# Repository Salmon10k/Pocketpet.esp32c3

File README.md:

# Pocketpet.esp32c3

> **Status (2026-11-14): active again, in small steps.** The project was paused on 2026-10-30 and picked back up
> for the games/menu revamp (11-12) and a repo review (11-14). A lot of the firmware on `main` (Online, Spotify,
> Lyrics visual, games, launcher) is still **not fully tested on the device**, and the custom PCB is designed but
> not finished or ordered (`PCB/` holds the KiCad project only). See `HANDOFF.md` for the details.
> Do not start big new features unless Salman asks.

Keychain-sized digital pet gadget built around an ESP32-C3 Super Mini with a 1.3" SH1106 OLED, MPU6050 motion sensor, touch input and three buttons.

## Current hardware wiring

**Important:** the OLED and MPU6050 share **one hardware I2C bus (`Wire`)** on GPIO 8 (SDA) and GPIO 9 (SCL), 400 kHz. They have different addresses (OLED `0x3C`, MPU6050 `0x68`), so they coexist on the same two wires. (Until 2026-11-09 the MPU6050 was on its own software I2C bus on GPIO 5/6; that is gone and GPIO 5/6 are free.)

| Part | Pin | ESP32-C3 GPIO | Notes |
|------|-----|---------------|-------|
| OLED SH1106 + MPU6050 | SDA | **8** | Shared hardware I2C, 400 kHz |
| OLED SH1106 + MPU6050 | SCL | **9** | Shared hardware I2C, 400 kHz |
| Button A | one leg to GND | **2** | Up / previous / tickle |
| Button B | one leg to GND | **1** | Select / back |
| Button C | one leg to GND | **0** | Down / next / boop |
| Touch pad | OUT | **4** | TTP223-style, HIGH when touched (the pin next to 3V3) |

Wire the MPU6050 SDA/SCL to the same GPIO 8 / 9 pins as the OLED.

### I2C addresses
- OLED: `0x3C`
- MPU6050: `0x68`

### GPIO notes
- GPIO 8 and GPIO 9 are ESP32-C3 strapping pins (they are also the C3's default I2C pins). The OLED has been tested on them. If the board ever becomes unreliable during boot, investigate these pins first.
- GPIO3 is the only free ADC1 pin left. Keep it for the battery voltage divider.
- GPIO 0-5 can wake the C3 from deep sleep, so the touch pad (GPIO4) and buttons (0, 1, 2) all work for wake-up later.

## Current firmware

### Home and menu
The **pet is the home screen**: it is what you see when the keychain turns on and where it returns to when you leave it alone (the launcher goes back to the pet after 20 s without input; holding B in the launcher also goes home). **Press B on the pet** to open the launcher, which has two styles you pick in **Settings > Menu style**:
- **Carousel** (default): big icons slide in from the right; **A** = previous, **C** = next, **B** = open.
- **Tilt ring**: the apps sit on a ring; **tilt the keychain toward an app** to highlight it, **B** opens it (A/C also step through them).

In the launcher: Fluid, Stats, Motion test, Tools, Games, Online, Spotify, Visualizer (Lyrics visual), Living OLED, Settings. While it starts, the MPU6050 calibrates itself in the background (gyro offsets, and which way is "down" from gravity), so tilt works however the sensor sits on the board and however you hold the keychain; in Pet mode it re-levels itself when you hold it still in a new pose. Every sub-menu (Tools, Games, Settings and the Online list) uses the same carousel / tilt-ring look as the home screen: **A/C** move, short **B** opens, **hold B** goes up one level, and each one ends with a **Back** item. Settings shows the current value in a pill under the name (brightness, screen auto-off, flip screen, menu style, lyrics sync, reset pet); Games shows your best score. Tools contains Temperature, Magic 8-ball and Dice (shake the keychain to roll / ask).

### Games
Built for the three buttons and the MPU6050. Best scores are saved.

| Game | Controls |
|------|----------|
| **Star Blaster** (side-scrolling shooter: drones, gunships, splitting rocks, power-ups) | tilt flies the ship, **A** shoots (hold = rapid fire), **C** = smart bomb |
| **Sniper** (night city, scope with sway; enemies pop up in windows, survive 3 misses) | tilt swings the scope, **A** fires (bolt action), hold **C** to steady your breath and zoom 2x |
| **Road Rush** (pseudo-3D racer, beat the clock, checkpoints add time) | tilt steers (bends push you outwards), **A** nitro, **C** brake |
| **Pinball** (the table lies on its side, flippers on the right edge) | **A** upper flipper, **C** lower flipper, shake the keychain to nudge the ball (nudge too much = TILT) |
| **Tilt Maze** | tilt, **A** re-zero, **C** new maze |
| **Snake** | tilt to steer (or **A** left / **C** right) |

Online has 12 screens that need the internet (see below). Copy `src/secrets.example.h` to `src/secrets.h` and set `WIFI_SSID` / `WIFI_PASSWORD` locally first. The touch pad only works in Pet mode.

### Online mode
Wi-Fi stays **off** everywhere except Online mode. Entering Online connects **once** (up to 3 automatic attempts, then each request is retried up to 3 times for random network hiccups), fetches everything for every screen in one go, and stays connected while you browse. Leaving Online switches the radio off. The list header shows the state: `wifi 2/3`, `sync 4/9`, `online`, `offline`. Every screen shows how old its data is (top right). If a refresh fails you keep the last good data.

**Several Wi-Fi networks:** list them in `secrets.h` with `WIFI_NETWORKS` (see `src/secrets.example.h`), for example home, uni and your phone hotspot. On entering Online it scans, tries the strongest known network first and falls back to the others by itself. Net status shows which one it picked. 2.4 GHz networks only.

Controls: in the list, A/C move and B opens (**Sync now** refetches everything, **Back** leaves). On a screen, **A = refresh this screen** (no reconnect), **C = next screen**, **B = back to the list**, touch = Home.

| Screen | Source (no API keys) | Refreshes |
|--------|----------------------|-----------|
| Clock | NTP (`pool.ntp.org`), keeps ticking offline | synced on connect, resync every 6 h |
| Weather | Open-Meteo | 30 min |
| Forecast | same request as Weather | 30 min |
| Air quality | Open-Meteo air quality (US AQI, PM2.5) | 30 min |
| Currency | open.er-api.com (USD to `CURRENCY_HOME`, EUR, GBP) | 6 h |
| World clocks | computed from NTP time, with DST rules for London, New York, Tokyo, Sydney | no request |
| Random fact | uselessfacts.jsph.pl | once per visit, A = new one |
| Advice | adviceslip.com | once per visit, A = new one |
| Moon phase | calculated from the date (approximate, within about a day) | no request |
| Net status | RSSI, IP, a `generate_204` check with ping time | every 20 s while open |
| ISS tracker | api.open-notify.org (plain HTTP) | every 60 s while open |
| GitHub | api.github.com stars, forks, issues, last push | 10 min |

Location for weather and air quality comes from an IP lookup (ip-api.com) unless you set `LOCATION_LAT` / `LOCATION_LON` in `secrets.h`. See `src/secrets.example.h` for all optional overrides.

**Pet reactions:** when cached data exists, Pet mode shows tiny corner icons: sweat drop (35 C or hotter), umbrella (rain chance 60% or more), cloud (AQI 150 or more), moon (after sunset). Each successful fetch also gives the pet a small happiness bump.

Requests are blocking with a 7 second timeout, so the screen can pause briefly while one runs. A progress frame is drawn first so it never looks frozen. Background refresh while you are in Online: weather and air quality every 30 min, currency 6 h, GitHub 10 min. Net status and ISS only refresh while you are looking at them.

**Connection problems:** many ESP32-C3 Super Mini boards fail to connect at full TX power, so the firmware lowers it to 8.5 dBm by default. If your router is far away and the signal is weak, put `#define WIFI_TX_POWER WIFI_POWER_11dBm` (or `WIFI_POWER_19_5dBm`) in `src/secrets.h`.

### Spotify mode
Shows what is playing on your Spotify (any device: phone, PC, speaker), with **synced lyrics** from LRCLIB, and controls it: **A** previous, **B** play/pause, **C** next. **Hold B** (0.7 s) = back to the menu. The screen stays on while you are in this mode. Needs Spotify **Premium** for the buttons (viewing works without) and the Wi-Fi from `secrets.h`. Spotify itself must be playing somewhere; the keychain is a remote, not a speaker.

One-time setup (on your PC):
1. https://developer.spotify.com/dashboard -> Create app (any name, Web API). Add the Redirect URI exactly `http://127.0.0.1:8888/callback`. Copy the Client ID.
2. `python tools/spotify_auth.py YOUR_CLIENT_ID --write` (opens a Spotify login page, then writes `SPOTIFY_CLIENT_ID` and `SPOTIFY_REFRESH_TOKEN` into `src/secrets.h`, which Git ignores).
3. Build and flash. If it says the login expired (about every 6 months), run step 2 again.

Notes: Spotify apps in development mode need the app owner to have Premium and allow 5 users, which is plenty for one keychain. The screen can freeze for about a second when a song changes (a new secure connection for the lyrics), that is normal. Not every song has synced lyrics; those show the title and artist instead.

### Fluid mode
Particle water simulation that follows tilt. Hold the device like a phone, it calibrates for half a second (that pose counts as level). A = re-zero, C = Water / Honey / Mercury, B = back.

### Pet mode (companion style, nothing can die)
- Eyes ease smoothly between moods, blink on their own, sometimes double-blink or wink, and wander around when idle.
- Pupils follow tilt from the MPU6050.
- **Moods:** neutral, happy, sad (when ignored), sleepy (low energy or no activity for 30 s), asleep (no activity for 60 s, with floating Zzz).
- **Touch:** tap = love face and hearts. Hold the pad for 0.6 s = purr, which keeps raising happiness.
- **Motion:** shake = dizzy spiral eyes (and a small happiness drop). A sharp pickup, bump or drop = surprised.
- **Buttons in Pet mode:** A = tickle (laughs), C = boop (surprised), B = back to the menu.
- Any touch, button press or movement wakes it up.
- **Music pet (Settings > Music pet, default On):** while Spotify is playing, Pet mode quietly opens a Spotify session (Wi-Fi, so it costs battery; it drops when the screen turns off or you leave Pet mode) and the pet dances to the song. The reaction depends on the vibe: **Chill** (eyes closed, headphones, slow sway), **Pop** (happy eyes, bounce, notes and sparkles), **Hype** (shades, head nods, impact lines), **Rock** (angry eyes, headbang, lightning), **EDM** (big pulsing pupils, equalizer, strobe on the bar), **Desi** (dreamy eyes, wide sway, hearts), **Dreamy** (starry eyes, twinkles). The mouth flaps on sung words. The vibe name flashes briefly when a track starts; a trailing **?** means it was guessed (no genre data) from the title and lyric speed. The beat is a steady feel-tempo per vibe locked to the song position, not the song's real BPM (Spotify no longer gives tempo).

### Stats
Happiness and energy are saved to flash (about every 2 minutes when they changed, and when leaving Pet mode), so the pet remembers across reboots. The Stats screen shows both bars and a lifetime pet count. **A or C flips it to a System page** with the numbers that matter for debugging: FPS (frames sent to the OLED, capped at 25), how often `loop()` runs, free heap, lowest free heap since boot, the largest free block (the real limit for a TLS connection), app size, uptime and why the chip last restarted. Open it before and after using Online or Spotify to see how much heap they eat.

### Other
- Button debouncing with press events.
- MPU6050 and OLED are re-checked every 2 seconds and recover if they drop out.
- Serial diagnostics once a second (buttons, touch, OLED, MPU, happy, energy, pets, fps, free / min heap and largest free block in KB).
- GitHub Actions (`.github/workflows/build.yml`) builds the firmware with PlatformIO on every push and shows the RAM / flash usage in the run summary.

## Build

1. Install PlatformIO in VS Code.
2. Open this folder (it will download U8g2 and ArduinoJson).
3. Plug the ESP32-C3 Super Mini in with a data-capable USB cable.
4. Build and upload with PlatformIO.
5. Board environment: `esp32-c3-supermini`.
6. USB CDC on boot is enabled in `platformio.ini`.
7. `partitions.csv` gives the app a 3 MB slot (no OTA) because Wi-Fi + TLS made the firmware too big for the default 1.3 MB slot.

## Files
- `src/main.cpp` -> main firmware and pet logic
- `src/online.h` / `src/online.cpp` -> Online mode (Wi-Fi state machine, request cache, the 12 screens)
- `src/vibe.*` -> genre to vibe classification, feel-tempo, energy (pure C++)
- `src/pet_face.*` / `src/pet_music.*` -> pet eyes and mouth drawing; per-vibe dance poses and decorations
- `src/spotify.h` / `src/spotify.cpp` -> Spotify mode (token refresh, now playing, controls, LRCLIB lyrics)
- `tools/spotify_auth.py` -> one-time Spotify login helper (PC)
- `src/config.h` -> all GPIO assignments, I2C addresses and pet tuning
- `platformio.ini` -> PlatformIO build configuration
- `partitions.csv` -> flash layout (one 3 MB app slot)

When changing wiring, update `src/config.h` first.

## First-flash checklist
- [ ] Builds and uploads
- [ ] OLED shows the menu (serial boot log says "OLED found")
- [ ] Serial shows `mpu=1`
- [ ] `touch=` flips to 1 when the pad is touched
- [ ] Eyes follow tilt the right way (if not, flip `TILT_X_SIGN` / `TILT_Y_SIGN` in `config.h`)
- [ ] Shake gives dizzy eyes, sharp pickup gives surprised eyes

## Status
- [x] Repo + starter project
- [x] OLED confirmed working (SH1106, GPIO 8/9)
- [x] Touch pad soldered on, signal on GPIO4
- [x] I2C roles swapped: OLED on hardware I2C, MPU6050 on SoftWire (superseded 2026-11-09: both now share the hardware bus on GPIO 8/9)
- [x] Improved pet mode: moods, eased eyes, touch petting, motion reactions, sleep, hearts, Zzz
- [x] Stats screen with flash-saved happiness and energy
- [x] Verify current firmware on hardware
- [ ] Try the RoboEyes library for the eyes (optional, only if the current look is not liked)
- [x] Temperature mode
- [x] Game mode (Magic 8-ball + Dice)
- [x] Games (Star Blaster, Sniper, Road Rush, Pinball, generated Tilt Maze, tilt Snake)
- [x] Touch pad (Pet mode only)
- [x] Optional Wi-Fi NTP clock (credentials must be configured locally in ignored `src/secrets.h`)
- [x] Wi-Fi NTP clock
- [x] Online mode: weather, forecast, AQI, currency, world clocks, fact, advice, moon, net status, ISS, GitHub (in code, host-checked, not yet tested on the device)
- [ ] Pet sleeps at night
- [ ] Battery monitoring (GPIO3 divider)
- [ ] Deep sleep / wake on touch

## Notes for future development

> **OLED + MPU6050 share one hardware I2C bus on GPIO 8 (SDA) / 9 (SCL).**

If another developer or AI agent continues this project, read `src/config.h` and this README before changing pin assignments or the bus setup. The pet logic is separated from the drawing: `currentFace()` decides the mood, `faceParams()` maps a mood to eye/mouth targets, and `drawPet()` eases toward them.

## Work completed today (2026-10-10)

Today’s development session focused on expanding the games and preparing the online clock feature:

- **Tilt Maze:** planned/prototyped a procedural maze system, with randomized maze generation, solvable layouts, reversed left/right tilt behavior, and a 45° forward-facing MPU6050 neutral angle.
- **Dino Runner:** expanded the design with jump/crouch controls, additional obstacle types, flying obstacles, and more polished movement/animation.
- **Online clock:** added the Wi-Fi/NTP clock direction, including local credential handling through the ignored `src/secrets.h` file and an example template at `src/secrets.example.h`.
- **Documentation:** updated the handoff notes and README to record the work from this session.

**Hardware status:** these new changes were not fully hardware-validated today. The existing Batch 1 hardware features remain the known-tested baseline. Do not treat the new maze, Dino upgrades, or Wi-Fi clock as hardware-confirmed until they are built, flashed, and tested on the device.

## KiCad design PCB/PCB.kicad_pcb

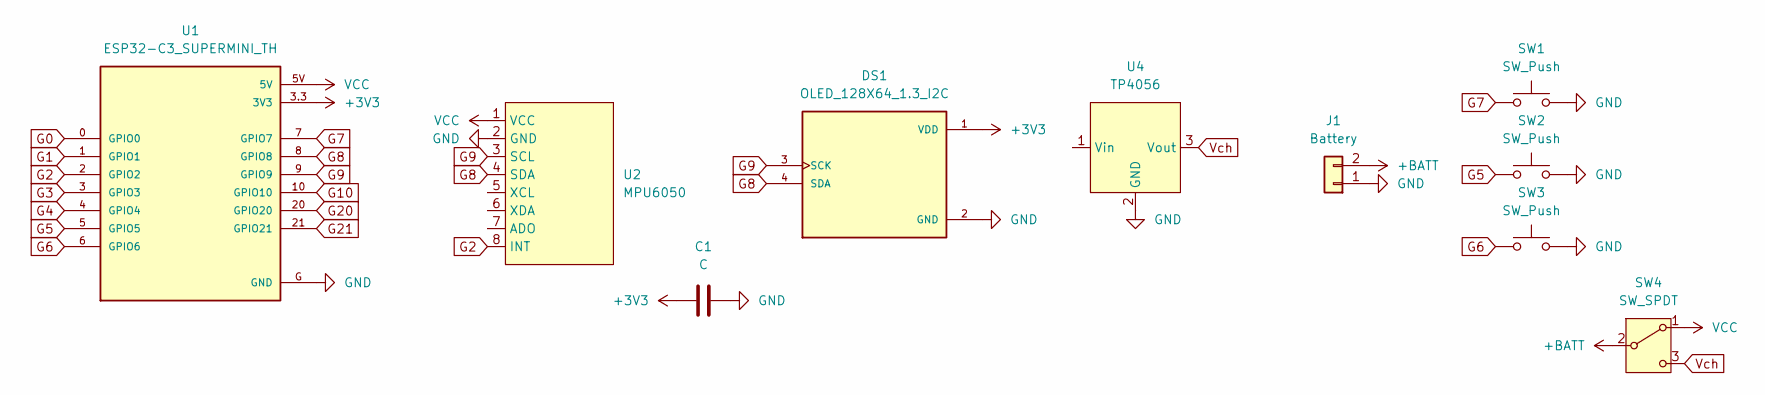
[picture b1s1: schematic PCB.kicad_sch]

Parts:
C1: C; C_0805_2012Metric_Pad1.18x1.45mm_HandSolder
DS1: OLED_128X64_1.3_I2C; LCD_OLED_128X64_1.3_I2C; PARTREV NA
J1: Battery; TerminalBlock_Phoenix_MPT-0,5-2-2.54_1x02_P2.54mm_Horizontal
SW1, SW2, SW3: SW_Push; SW_PUSH_6mm
SW4: SW_SPDT; SW_Slide_SPDT_Straight_CK_OS102011MS2Q
U1: ESP32-C3_SUPERMINI_TH; MODULE_ESP32-C3_SUPERMINI_TH
U2: MPU6050
U4: TP4056

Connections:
+3V3: C1.1, DS1.1 (VDD), U1.3.3 (3V3)
+BATT: J1.2, SW4.2 (B)
G0: U1.0 (GPIO0)
G1: U1.1 (GPIO1)
G2: U1.2 (GPIO2), U2.8 (INT)
G3: U1.3 (GPIO3)
G4: U1.4 (GPIO4)
G5: SW2.1, U1.5 (GPIO5)
G6: SW3.1, U1.6 (GPIO6)
G7: SW1.1, U1.7 (GPIO7)
G8: DS1.4 (SDA), U1.8 (GPIO8), U2.4 (SDA)
G9: DS1.3 (SCK), U1.9 (GPIO9), U2.3 (SCL)
G10: U1.10 (GPIO10)
G20: U1.20 (GPIO20)
G21: U1.21 (GPIO21)
GND: C1.2, DS1.2 (GND), J1.1, SW1.2, SW2.2, SW3.2, U1.G (GND), U2.2 (GND), U4.2 (GND)
VCC: SW4.1 (A), U1.5V, U2.1 (VCC)
Vch: SW4.3 (C), U4.3 (Vout)

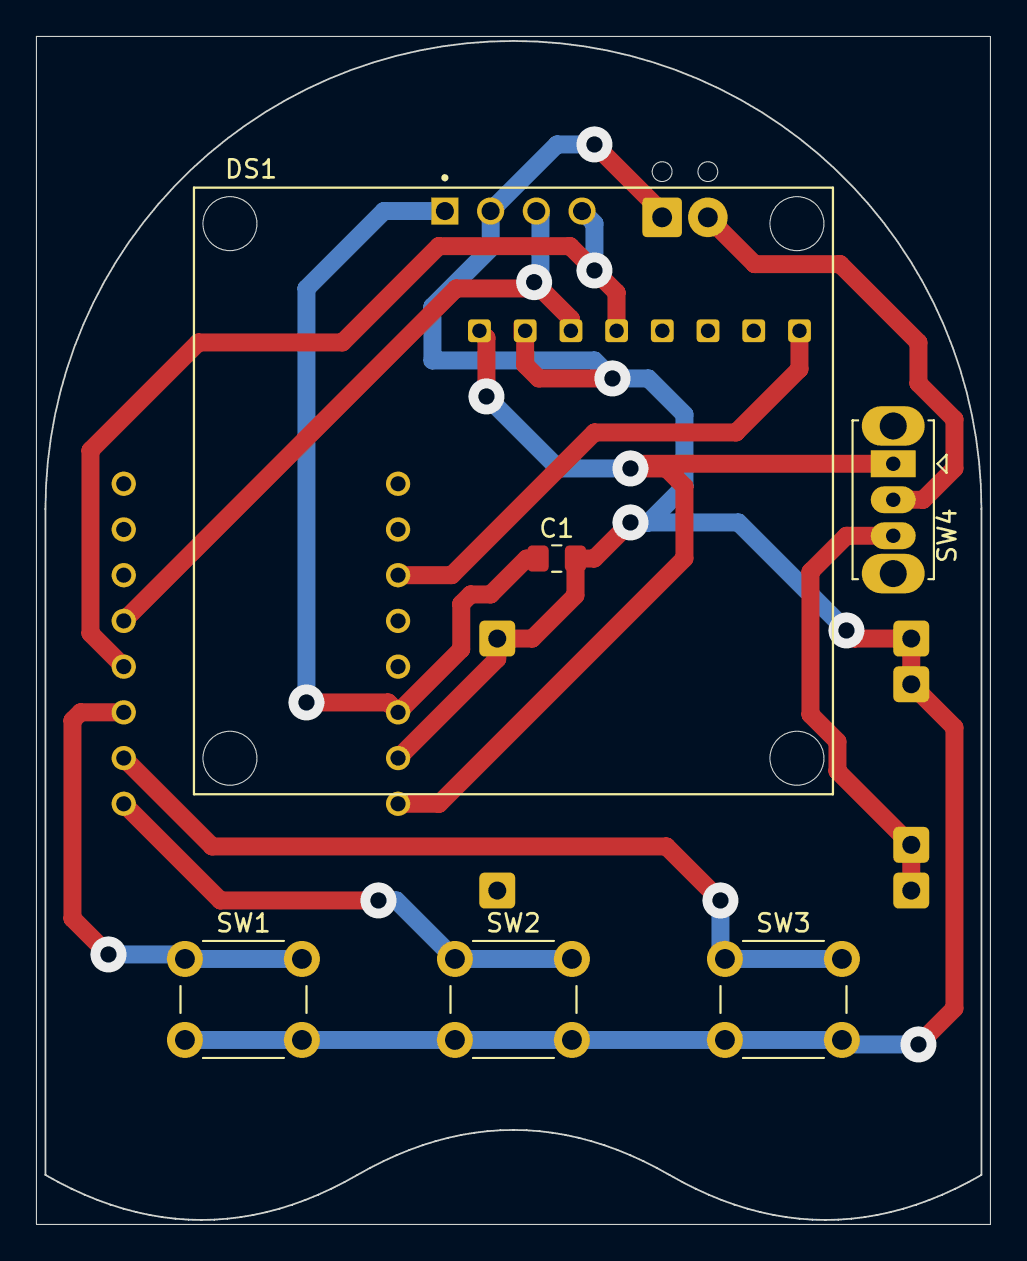
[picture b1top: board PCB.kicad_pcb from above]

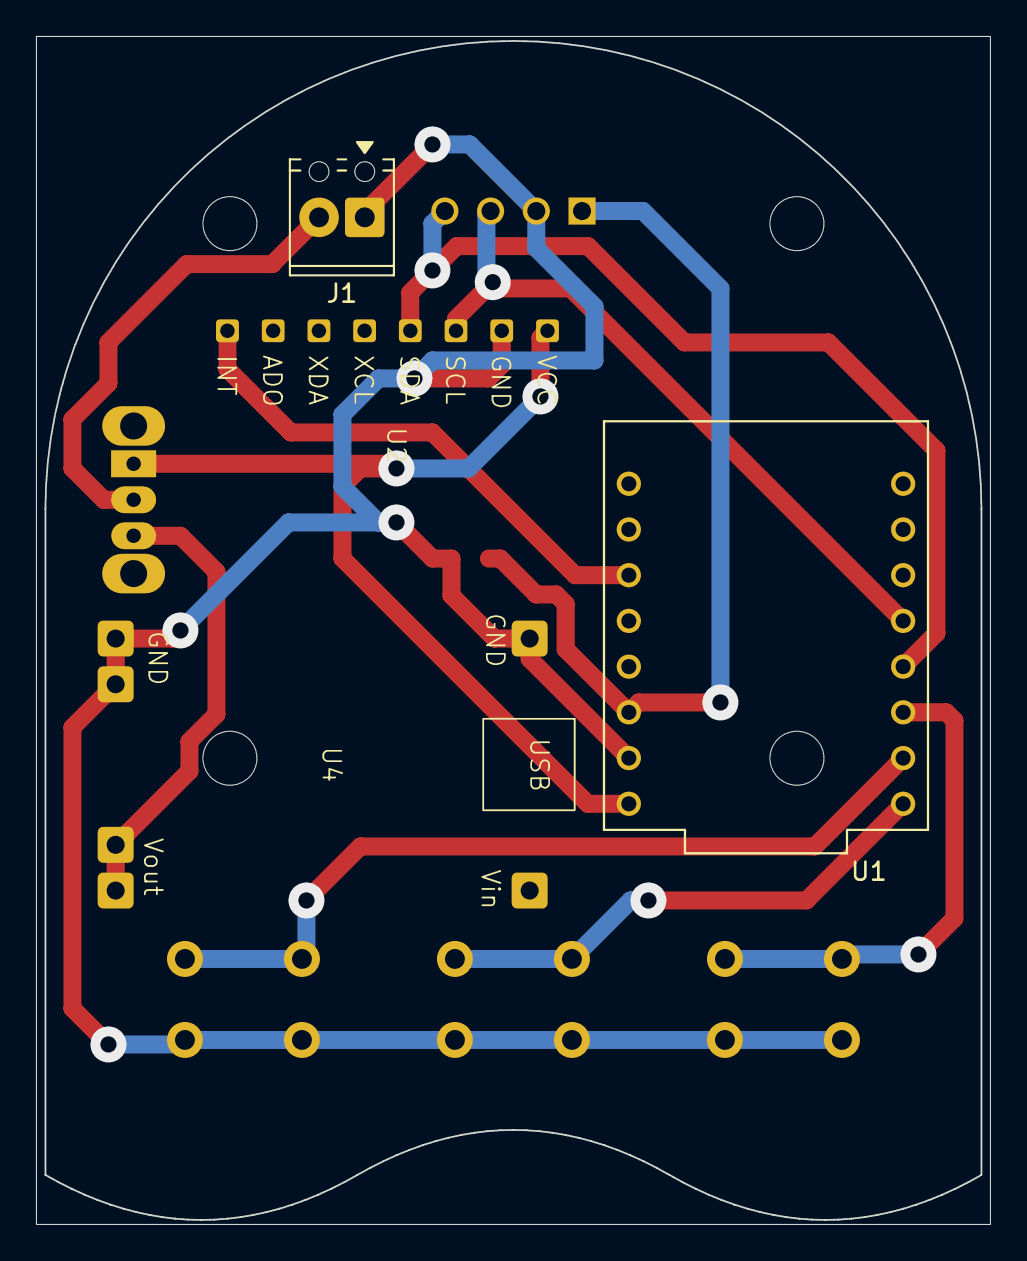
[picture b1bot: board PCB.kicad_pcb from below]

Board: 2 copper layers, 53.0 x 66.0 mm, 10 parts (4 on the bottom side), 11 nets.
